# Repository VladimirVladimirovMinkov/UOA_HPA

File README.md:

# UACHPA

This is a code and document repository for the University of auckland Aeronaughtics Club Human Powered Aircraft

# Overview

Repository Structure:
* Documents: This folder contains documents and reports made relating to the HPA
* CAD: Contains Computer Aided Design projects such as SOLIDWORKS or KiCAD
* src: This is for the code for the control systems and input mapping
* Test: This is the RnD folder for prototypes and demos that don't 100% work

# Getting involved
Please respect the repository structure and make sub folders if you're adding to the project so it is easier to navigate the repository

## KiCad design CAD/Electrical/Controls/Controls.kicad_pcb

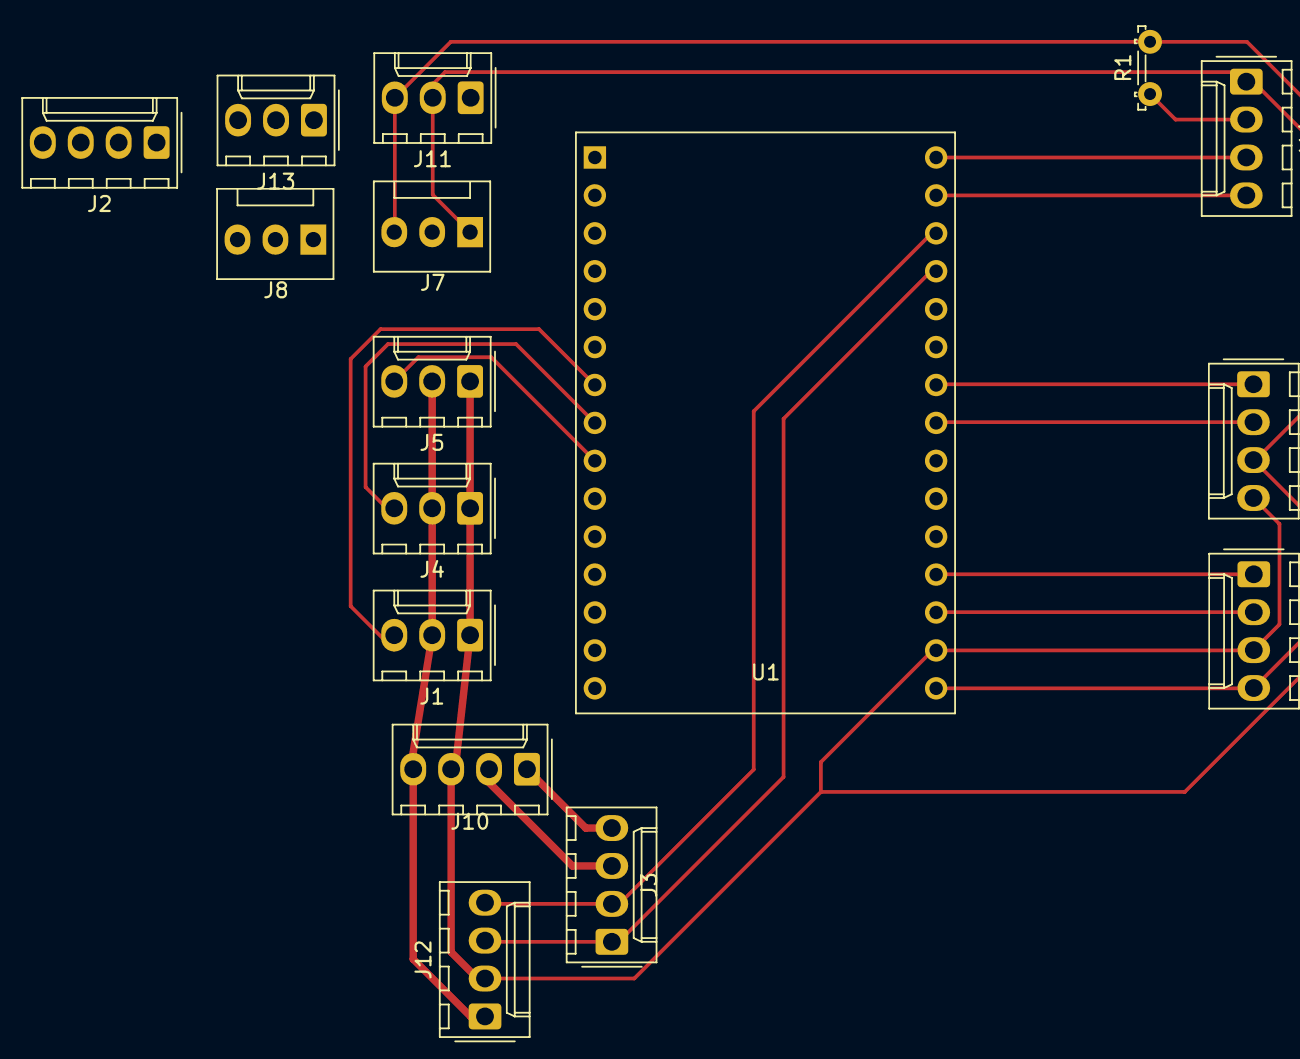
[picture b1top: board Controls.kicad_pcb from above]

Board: 2 copper layers, 16 parts (0 on the bottom side), 22 nets.

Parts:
J1: Aileron Servo; Molex_KK-254_AE-6410-03A_1x03_P2.54mm_Vertical
J2: pitot tube assembly; Molex_KK-254_AE-6410-04A_1x04_P2.54mm_Vertical
J3: External Connector; Molex_KK-254_AE-6410-04A_1x04_P2.54mm_Vertical
J4: Rudder Servo; Molex_KK-254_AE-6410-03A_1x03_P2.54mm_Vertical
J5: Elevator Servo; Molex_KK-254_AE-6410-03A_1x03_P2.54mm_Vertical
J6: BME280; Molex_KK-254_AE-6410-04A_1x04_P2.54mm_Vertical
J7: Pitch Control; FanPinHeader_1x03_P2.54mm_Vertical
J8: Roll Control; FanPinHeader_1x03_P2.54mm_Vertical
J9: SD card; Molex_KK-254_AE-6410-04A_1x04_P2.54mm_Vertical
J10: Battery and/or BMS; Molex_KK-254_AE-6410-04A_1x04_P2.54mm_Vertical
J11: Restart/Boot Button; Molex_KK-254_AE-6410-03A_1x03_P2.54mm_Vertical
J12: GPS; Molex_KK-254_AE-6410-04A_1x04_P2.54mm_Vertical
J13: Cadence Sensor; Molex_KK-254_AE-6410-03A_1x03_P2.54mm_Vertical
J14: Gyroscope; Molex_KK-254_AE-6410-04A_1x04_P2.54mm_Vertical
R1: Jumper; R_LDR_5.2x5.2mm_P3.5mm_Horizontal
U1: ESP32-C3-DevKitM-1

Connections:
unnamed: J1.1, J2.2, J4.1, J5.1, J6.3, J7.3, J8.3, J9.4, J10.3, J11.3, J12.2, J13.1, J14.2, R1.1, R1.2, U1.14 (GND), U1.17 (GND)
unnamed: J1.2, J4.2, J5.2, J10.4, J12.1, U1.15 (VIN)
unnamed: J1.3, U1.7 (D33)
unnamed: J2.3, U1.6 (D32)
unnamed: J2.4, U1.3 (VN)
unnamed: J4.3, U1.8 (D25)
unnamed: J5.3, U1.9 (D26)
unnamed: J6.1, U1.19 (D2)
unnamed: J6.2, U1.18 (D15)
unnamed: J7.2, U1.4 (D34)
unnamed: J8.2, U1.5 (D35)
unnamed: J9.1, U1.24 (D18)
unnamed: J9.2, U1.23 (D5)
unnamed: J3.4, J10.1
unnamed: J3.3, J10.2
unnamed: J11.1, U1.1 (EN)
unnamed: J2.1, J6.4, J7.1, J8.1, J9.3, J11.2, J13.2, J14.1, U1.16 (3.3V)
unnamed: J3.1, J12.3, U1.27 (RX0)
unnamed: J3.2, J12.4, U1.28 (TX0)
unnamed: J13.3, U1.2 (VP)
unnamed: J14.3, U1.30 (D23)
unnamed: J14.4, U1.29 (D22)

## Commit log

2025-02-24 Initialize repo
2025-02-24 Rearranged and added
2025-02-25 Added more electrical components
2025-02-25 Schematic update
2025-02-25 Mostly done schematic
    the voltage regulators are done
    need to rewire from dev board to esp32
    then PCB drawing
2025-02-25 BOM
    bill of materials
    there's an export function in KiCAD
    use python to split by " to get name and number used
2025-03-04 Schematic and almost BOM
2025-03-10 schematics and weight update
2025-03-20 update
    soon to break up the schematic
2025-04-21 note
    Just adding a note
2025-05-02 weight update and component change
2025-05-05 hole in rod
2025-07-26 Rejig and modify BOM
